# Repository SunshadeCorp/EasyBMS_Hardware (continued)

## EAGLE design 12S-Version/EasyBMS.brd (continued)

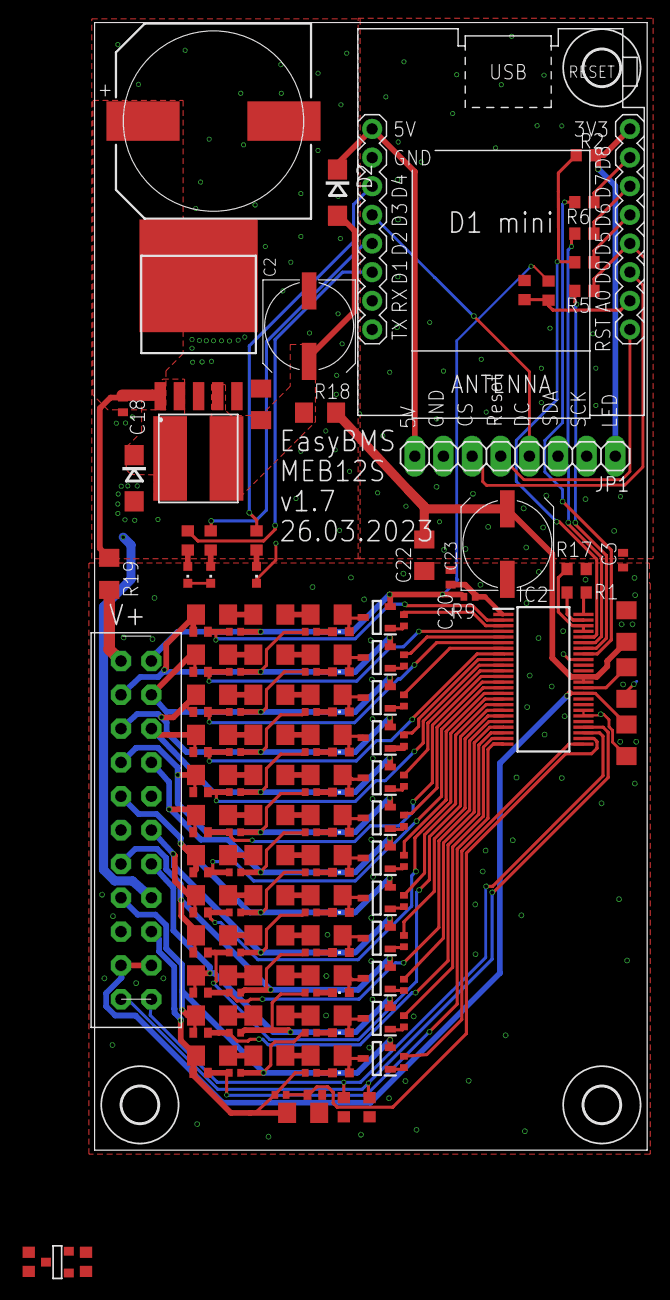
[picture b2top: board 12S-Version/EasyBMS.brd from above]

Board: 2 copper layers, 49.0 x 100.0 mm, 156 parts (0 on the bottom side), 136 nets.

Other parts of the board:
R55, R59: 10k; R0603
T1: C8545; SOT-23

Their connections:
5VINESP: R59.2; also elsewhere on the board
+3V3: R55.2, T1.3; also elsewhere on the board
unnamed: R55.1, T1.2
unnamed: R59.1, T1.1

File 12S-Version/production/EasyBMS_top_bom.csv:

Comment,Designator,Footprint,LCSC Part #
1k,R5 R6 R61 R62,R0603,
1uF,C1 C4 C19 C21 C22,C1206,
3.3k,R10 R22 R28 R34 R40 R46 R52 R68 R74 R80 R87 R93,R0402,
5K1,R2,R0603,
10R0,R4 R7 R8 R14 R20 R21 R25 R26 R27 R31 R32 R33 R37 R38 R39 R43 R44 R45 R49 R50 R51 R65 R66 R67 R71 R72 R73 R77 R78 R79 R84 R85 R86 R90 R91 R92,R1206,
10nF,C5 C6 C7 C8 C9 C10 C11 C12 C13 C14 C15 C16 C17,C0402,
12k,R57 R58,R0603,
20k,R17,R0603,
27K,R16,R0603,
100R,R1,R0603,
100R,R3 R9 R12,R0402,
100R,R19,R1206,
100R,R24 R30 R36 R42 R48 R64 R70 R76 R83 R89 R95,R0402,
100n,C3 C18 C20,C0402,
200R0,R53 R54 R56,R0603,
470R,R11 R23 R29 R35 R41 R47 R63 R69 R75 R81 R88 R94,R0402,
470k,R15,R0603,
BSS84LT1G,Q2 Q3 Q4 Q5 Q6 Q7 Q8 Q9 Q10 Q11 Q12 Q13,SOT96P237X111-3N,
C16015,D1 D2,DO214AC,
C249880,C2 C23,UD-8X10_NICHICON,
C249935,C24,WCAP-ASLI_16X17(DXL),
C370100,R13 R18,R1206,
C2929443,L1,CY75-100UH,
KT-0603R,LED1 LED2 LED4 LED5 LED6 LED7 LED8 LED9 LED11 LED12 LED13 LED14 LED15 LED16 LED17,CHIPLED_0603,
LM2596S-5.0_NOPB,IC1,KTT0005B,
LTC6811IG-1#PBF,IC2,SOP50P780X200-48N,

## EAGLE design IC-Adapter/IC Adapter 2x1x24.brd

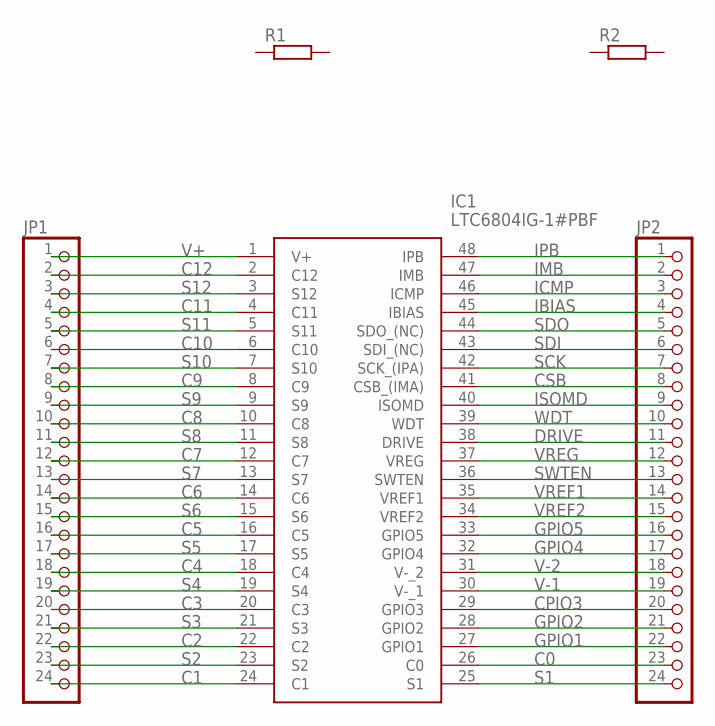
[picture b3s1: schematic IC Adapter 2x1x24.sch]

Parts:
IC1: LTC6804IG-1#PBF; SOP50P780X200-48N
JP1, JP2: PINHD-1X24; 1X24
R1, R2: R-EU_R1210; R1210

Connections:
C0: IC1.26 (C0), JP2.23
C1: IC1.24 (C1), JP1.24
C2: IC1.22 (C2), JP1.22
C3: IC1.20 (C3), JP1.20
C4: IC1.18 (C4), JP1.18
C5: IC1.16 (C5), JP1.16
C6: IC1.14 (C6), JP1.14
C7: IC1.12 (C7), JP1.12
C8: IC1.10 (C8), JP1.10
C9: IC1.8 (C9), JP1.8
C10: IC1.6 (C10), JP1.6
C11: IC1.4 (C11), JP1.4
C12: IC1.2 (C12), JP1.2
CPIO3: IC1.29 (GPIO3), JP2.20
CSB: IC1.41 (CSB_(IMA)), JP2.8
DRIVE: IC1.38 (DRIVE), JP2.11
GPIO1: IC1.27 (GPIO1), JP2.22
GPIO2: IC1.28 (GPIO2), JP2.21
GPIO4: IC1.32 (GPIO4), JP2.17
GPIO5: IC1.33 (GPIO5), JP2.16
IBIAS: IC1.45 (IBIAS), JP2.4
ICMP: IC1.46 (ICMP), JP2.3
IMB: IC1.47 (IMB), JP2.2
IPB: IC1.48 (IPB), JP2.1
ISOMD: IC1.40 (ISOMD), JP2.9
S1: IC1.25 (S1), JP2.24
S2: IC1.23 (S2), JP1.23
S3: IC1.21 (S3), JP1.21
S4: IC1.19 (S4), JP1.19
S5: IC1.17 (S5), JP1.17
S6: IC1.15 (S6), JP1.15
S7: IC1.13 (S7), JP1.13
S8: IC1.11 (S8), JP1.11
S9: IC1.9 (S9), JP1.9
S10: IC1.7 (S10), JP1.7
S11: IC1.5 (S11), JP1.5
S12: IC1.3 (S12), JP1.3
SCK: IC1.42 (SCK_(IPA)), JP2.7
SDI: IC1.43 (SDI_(NC)), JP2.6
SDO: IC1.44 (SDO_(NC)), JP2.5
SWTEN: IC1.36 (SWTEN), JP2.13
V+: IC1.1 (V+), JP1.1
V-1: IC1.30 (V-_1), JP2.19
V-2: IC1.31 (V-_2), JP2.18
VREF1: IC1.35 (VREF1), JP2.14
VREF2: IC1.34 (VREF2), JP2.15
VREG: IC1.37 (VREG), JP2.12
WDT: IC1.39 (WDT), JP2.10

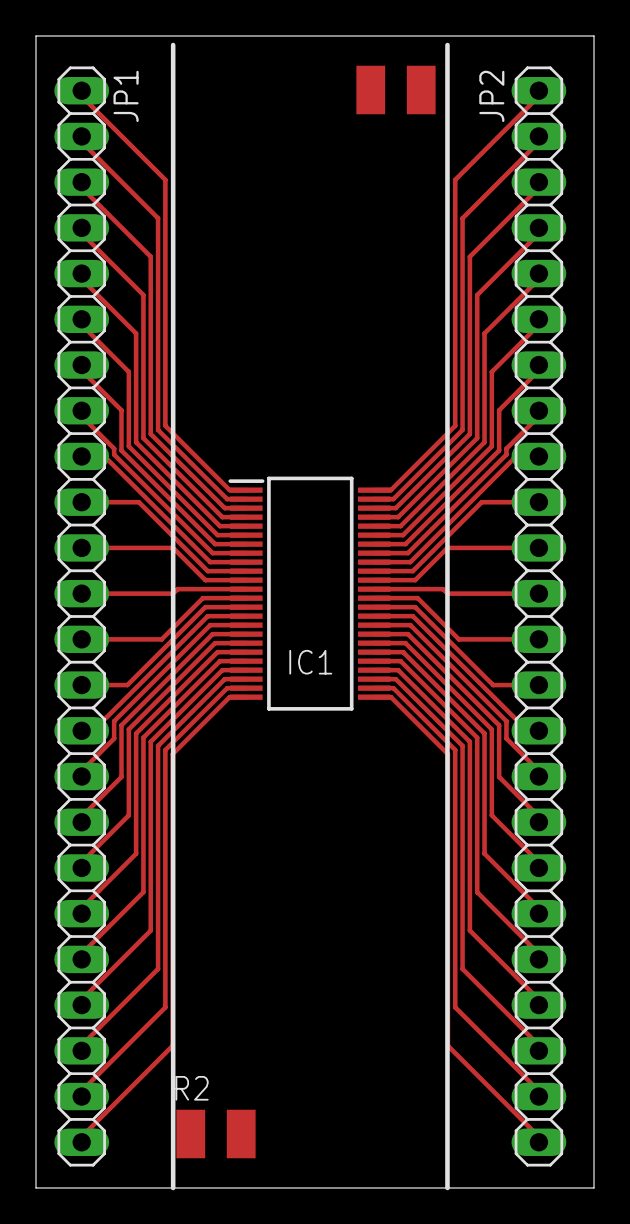
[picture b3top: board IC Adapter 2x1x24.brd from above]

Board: 2 copper layers, 31.0 x 64.0 mm, 5 parts (0 on the bottom side), 48 nets.

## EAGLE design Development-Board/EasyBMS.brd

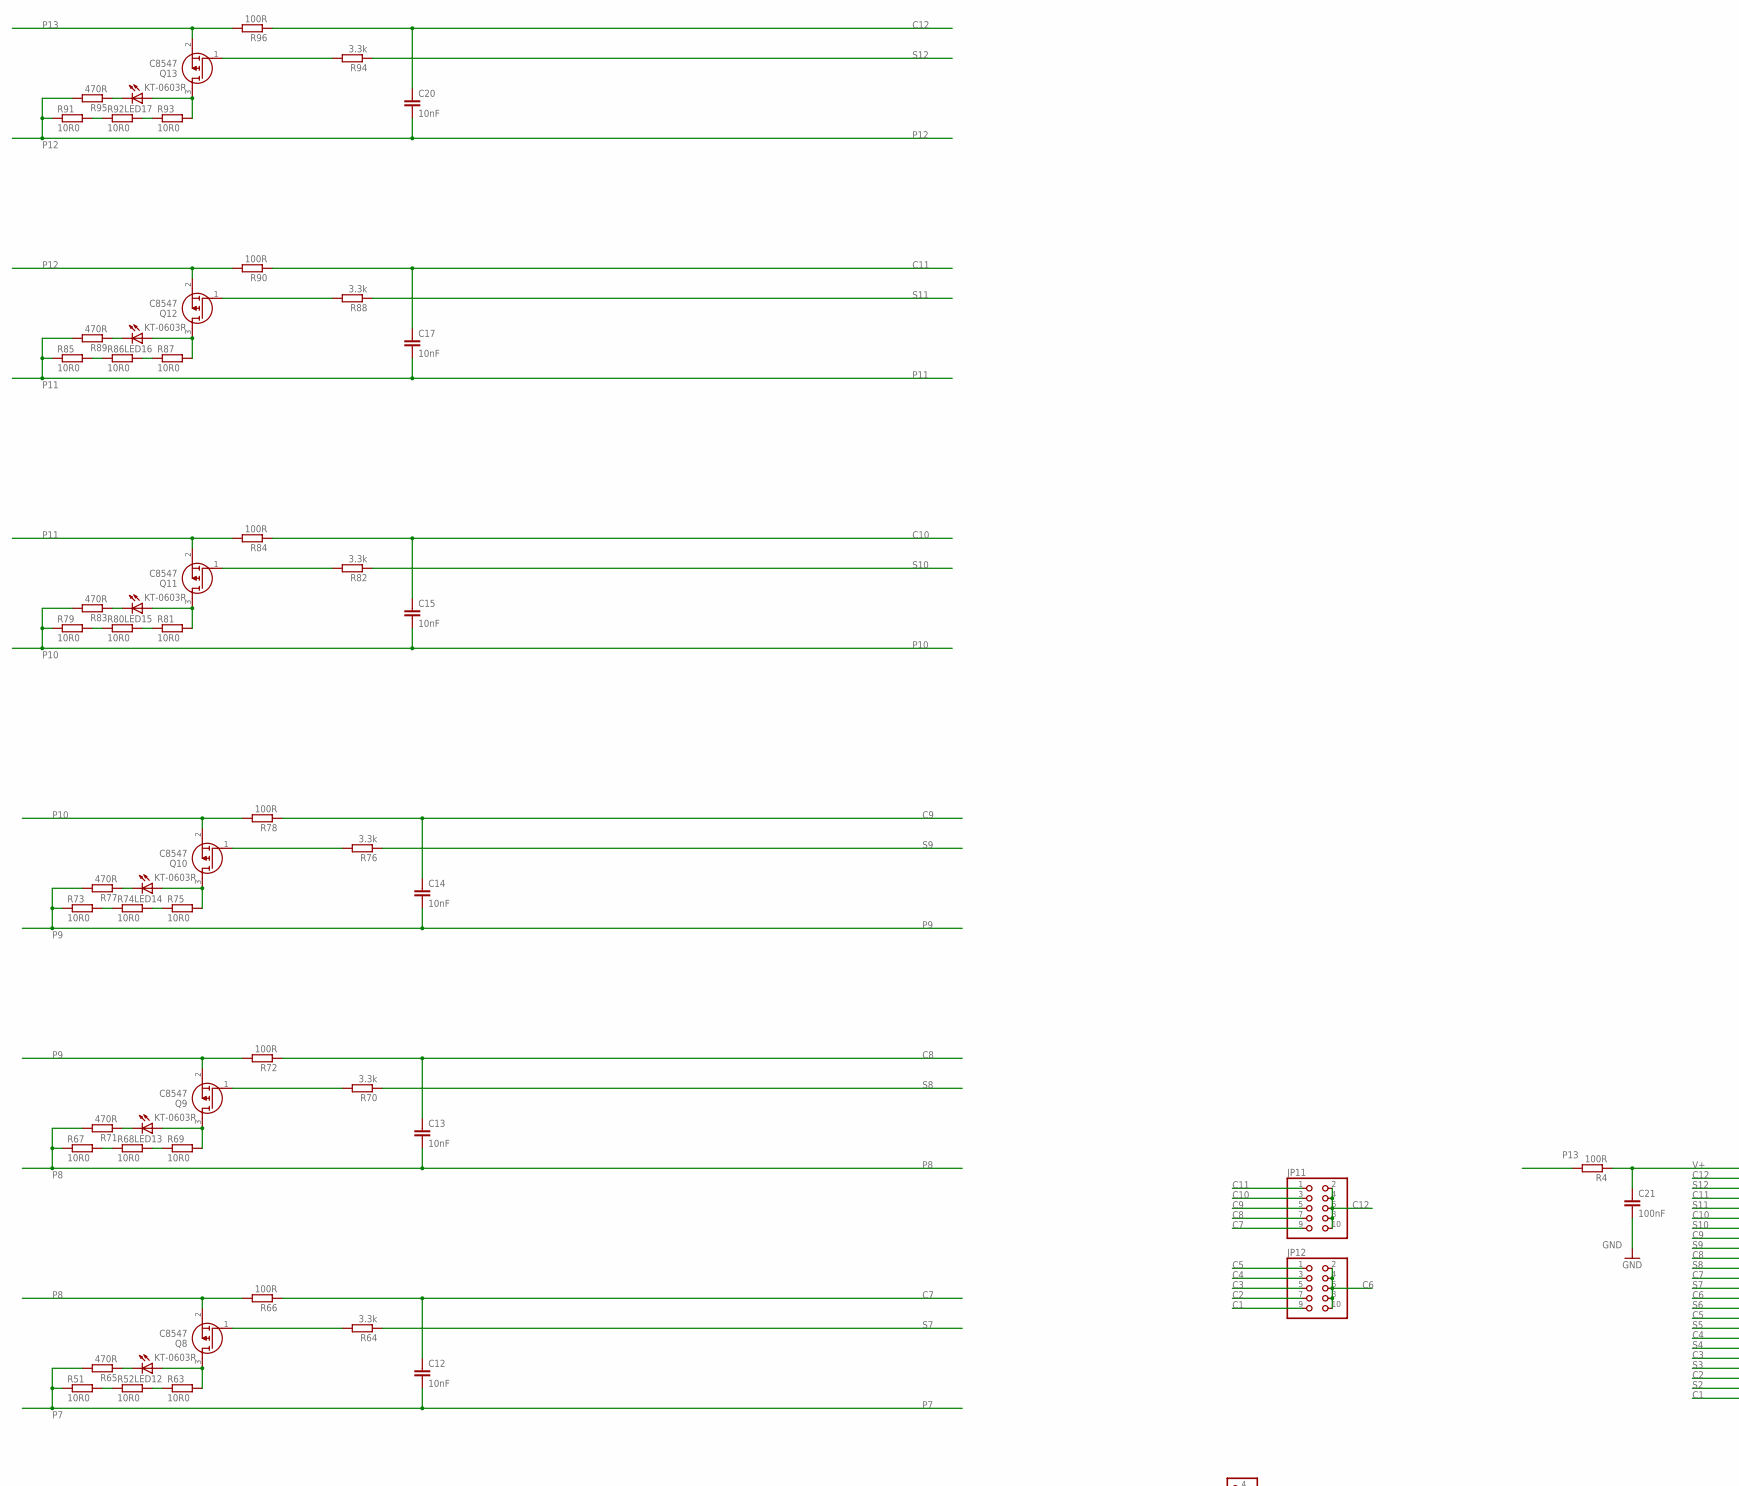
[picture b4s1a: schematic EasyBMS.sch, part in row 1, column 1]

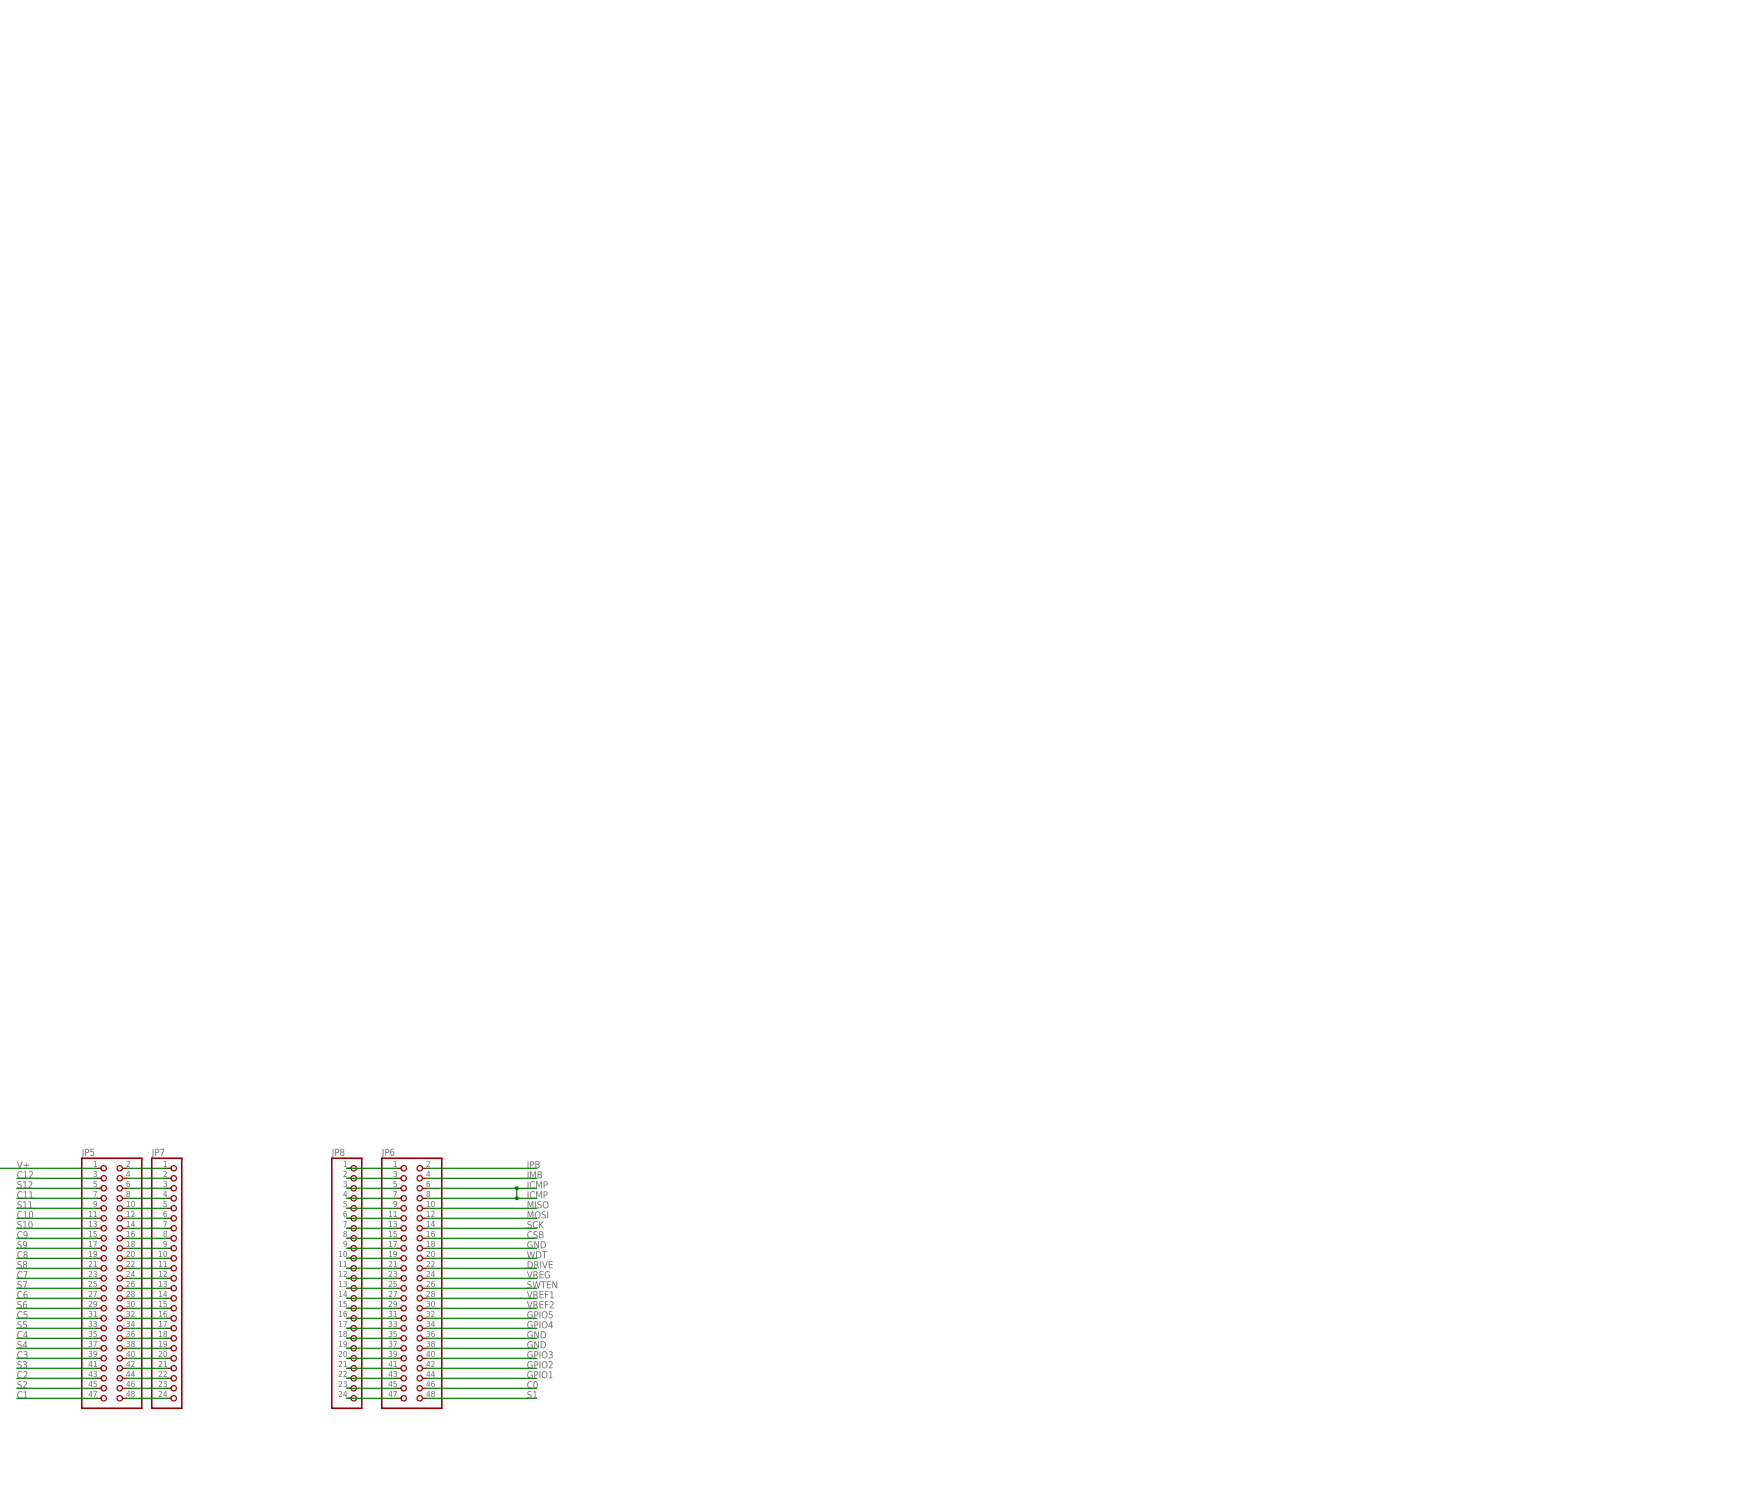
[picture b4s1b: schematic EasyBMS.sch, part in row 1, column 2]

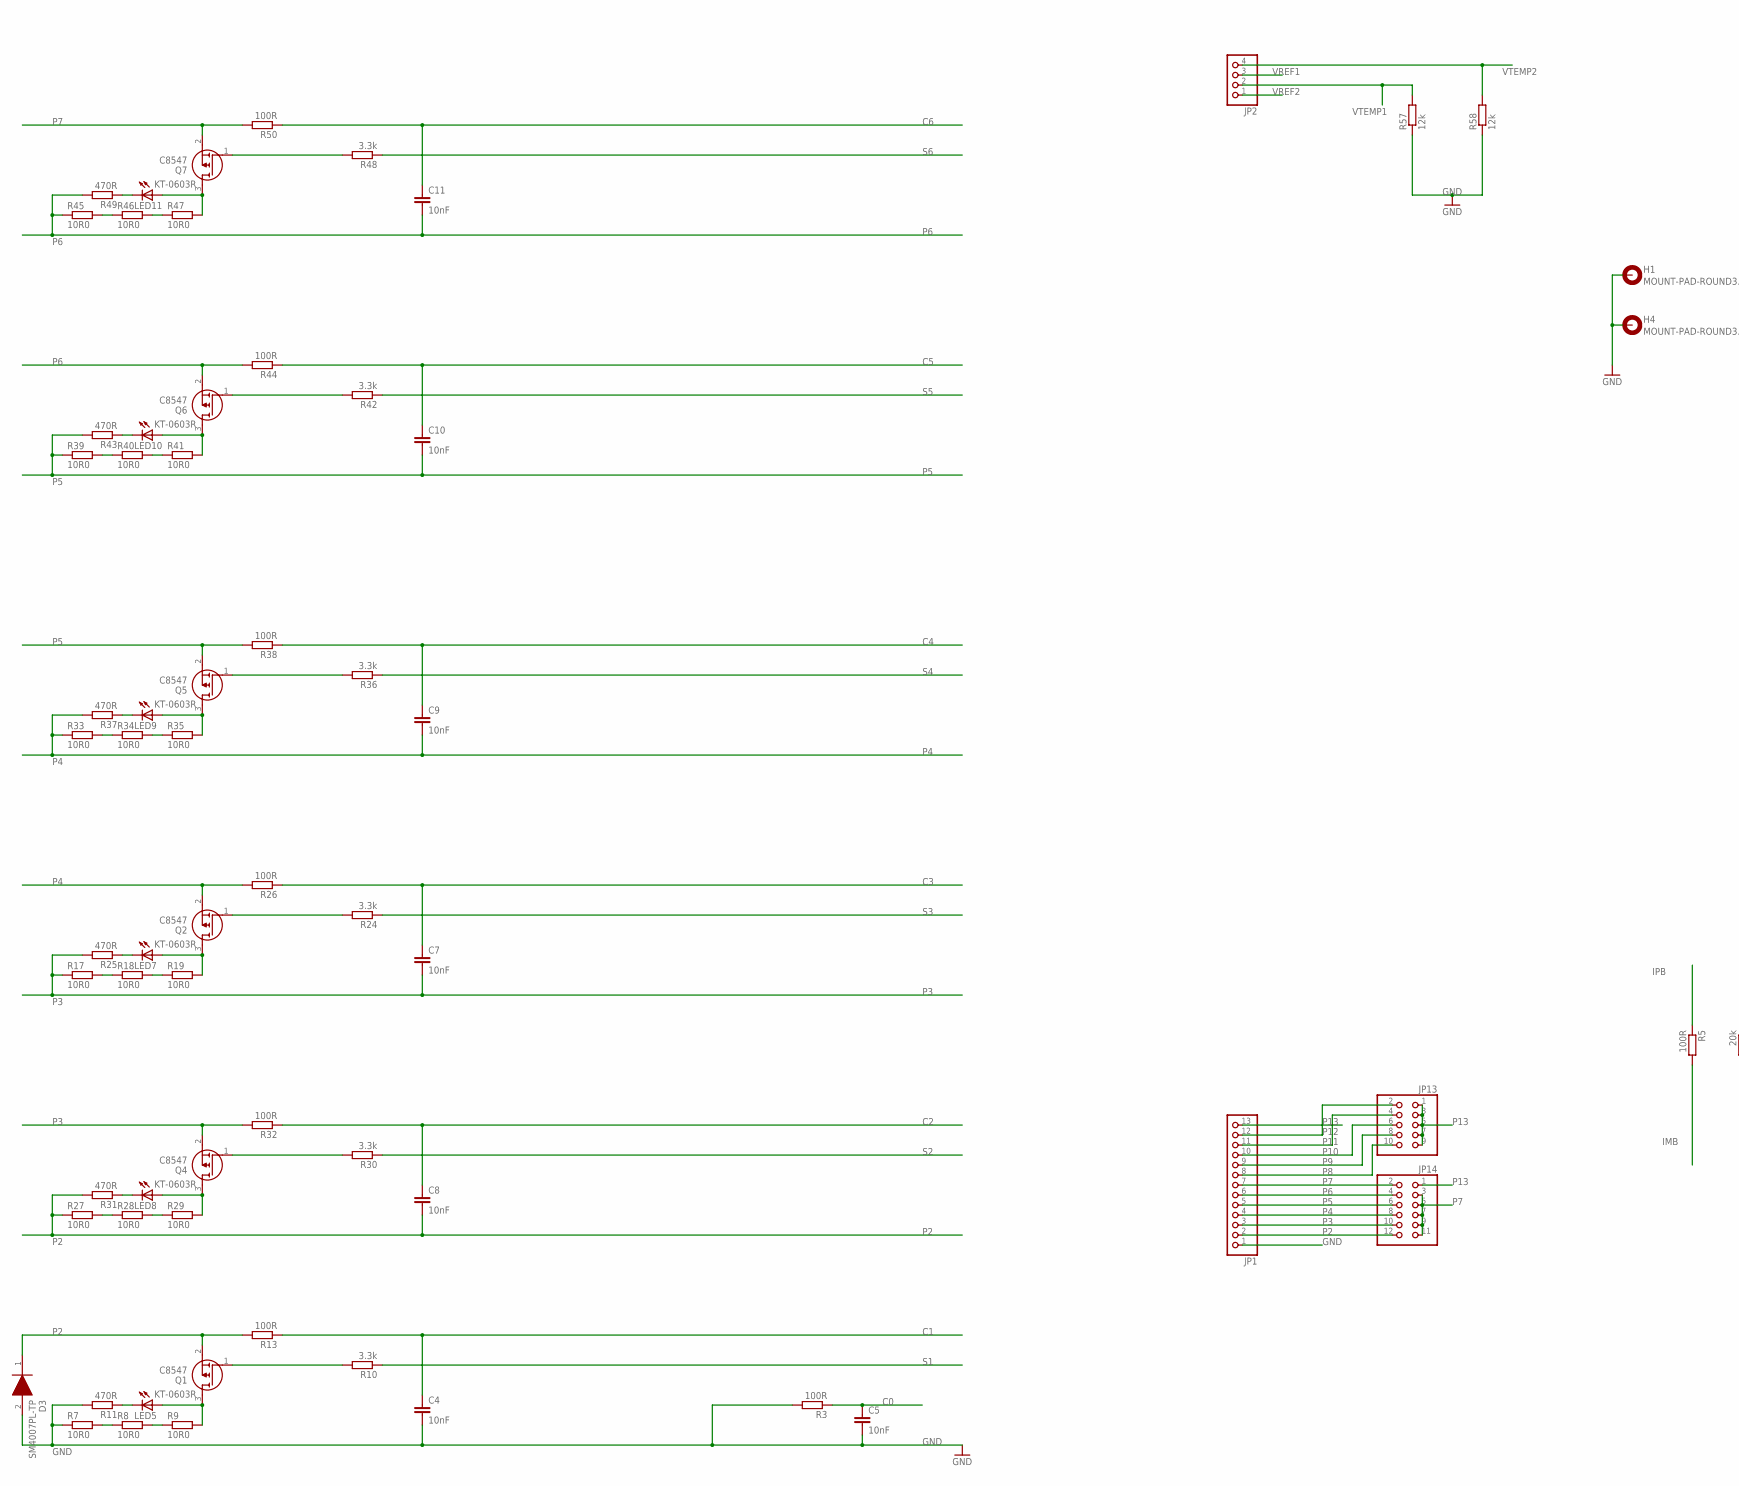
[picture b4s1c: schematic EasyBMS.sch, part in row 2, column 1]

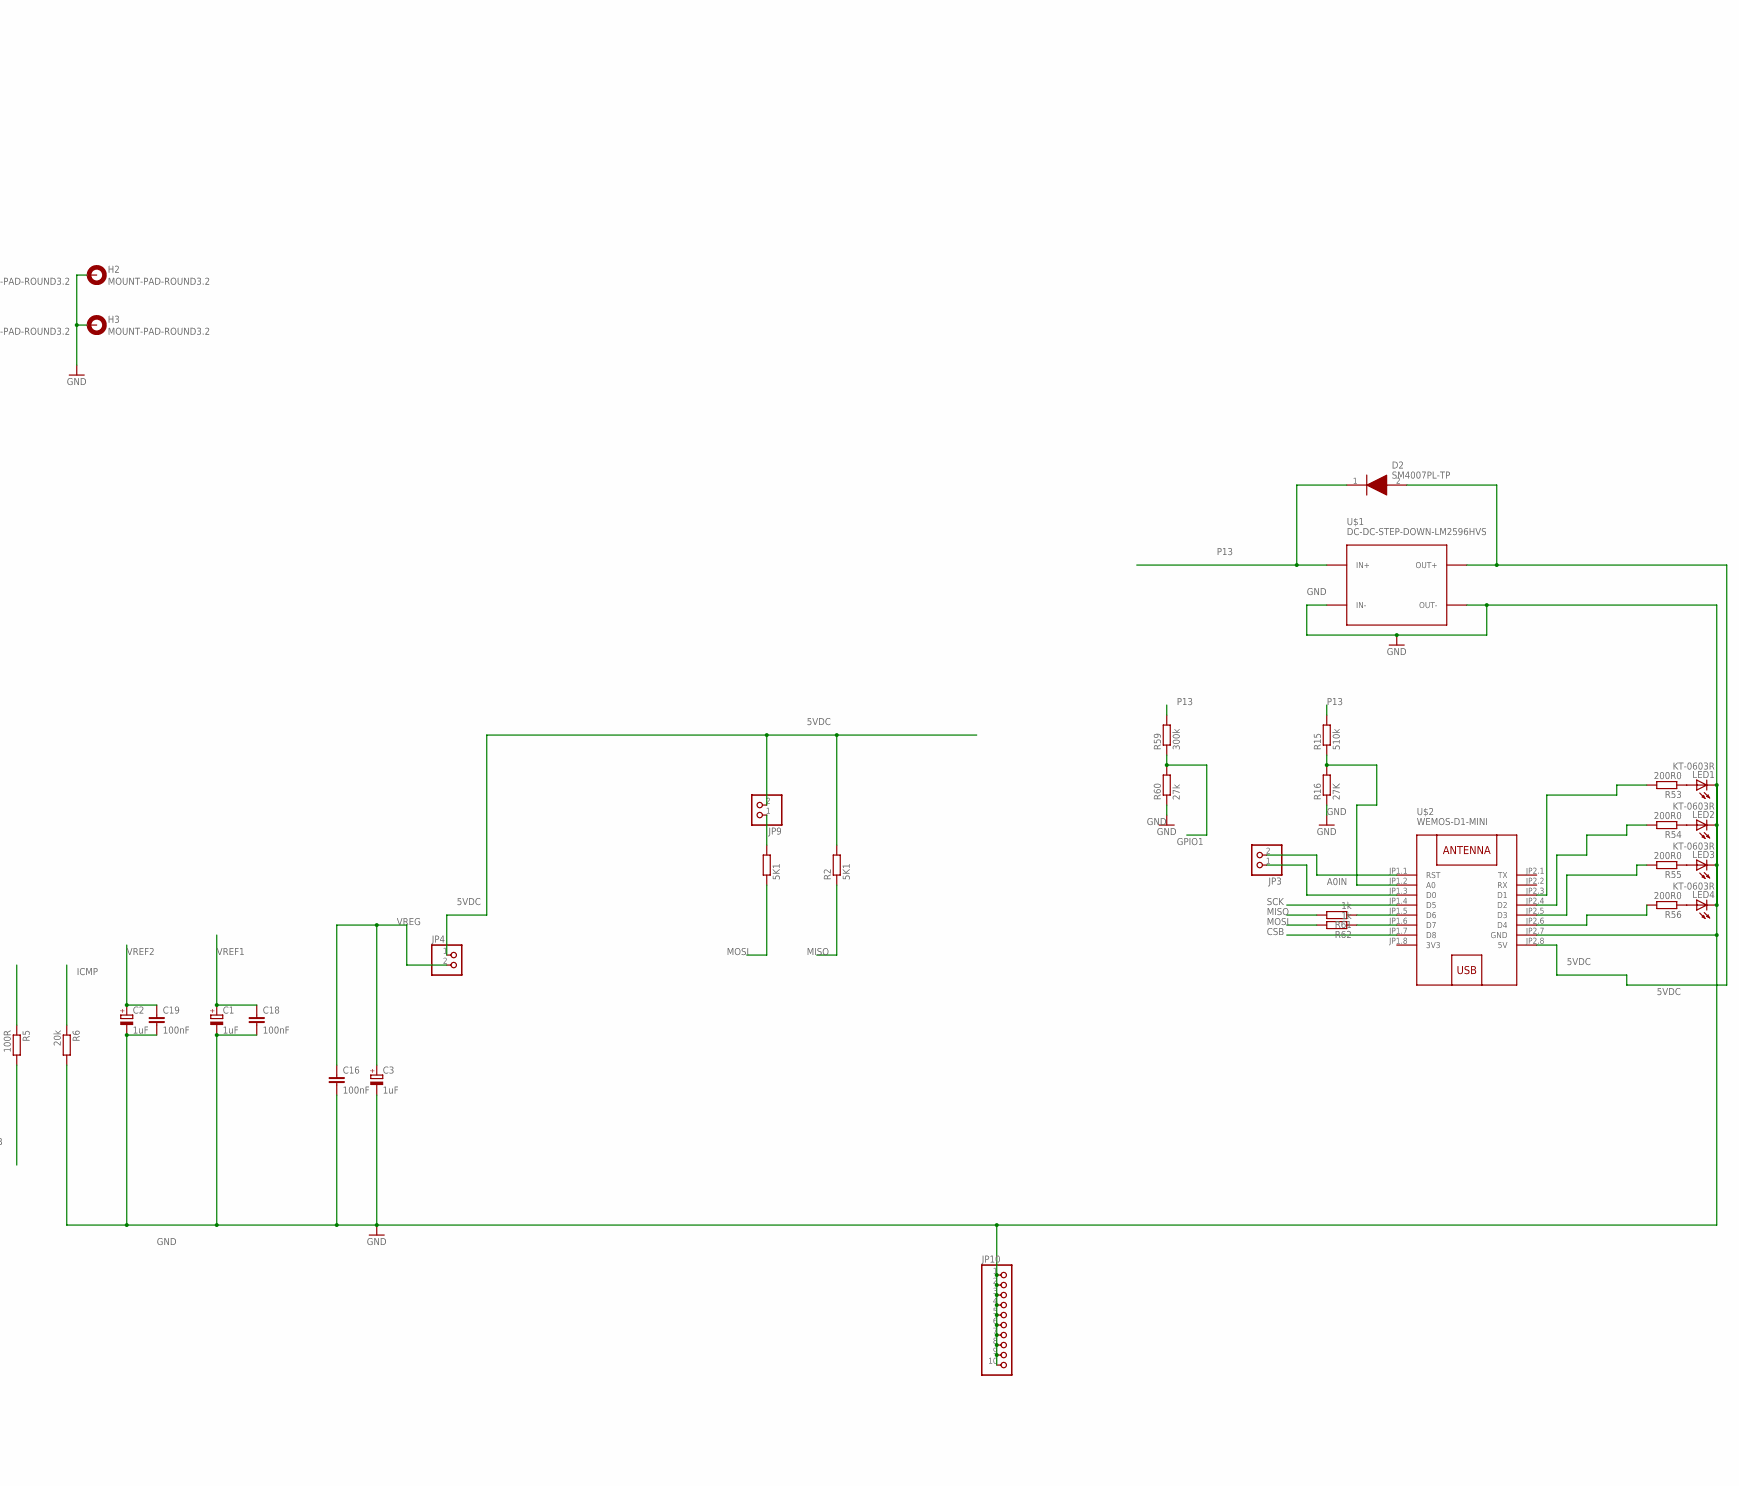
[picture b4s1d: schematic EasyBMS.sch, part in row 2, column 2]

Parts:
C1, C2, C3: 1uF; E2,5-6
C4, C5, C7, C8, C9, C10, C11, C12, C13, C14, C15, C17, C20: 10nF; C0402
C16, C18, C19, C21: 100nF; C1206
D2, D3: SM4007PL-TP; SODFL3616X135N
H1, H2, H3, H4: MOUNT-PAD-ROUND3.2; 3,2-PAD
JP1: PINHD-1X13/90; 1X13/90
JP2: PINHD-1X4/90; 1X04/90
JP3, JP4, JP9: PINHD-1X2; 1X02
JP5, JP6: PINHD-2X24; 2X24
JP7, JP8: PINHD-1X24; 1X24
JP10: PINHD-1X10; 1X10
JP11, JP12, JP13: PINHD-2X5; 2X05
JP14: PINHD-2X6; 2X06
LED1, LED2, LED3, LED4, LED5, LED7, LED8, LED9, LED10, LED11, LED12, LED13, LED14, LED15, LED16, LED17: KT-0603R; CHIPLED_0603
Q1, Q2, Q4, Q5, Q6, Q7, Q8, Q9, Q10, Q11, Q12, Q13: C8547; PG-SOT-23
R1, R2: 5K1; R0603
R3, R4, R5, R13, R26, R32, R38, R44, R50, R66, R72, R78, R84, R90, R96: 100R; R0402
R6: 20k; R0603
R7, R8, R9, R17, R18, R19, R27, R28, R29, R33, R34, R35, R39, R40, R41, R45, R46, R47, R51, R52, R63, R67, R68, R69, R73, R74, R75, R79, R80, R81, R85, R86, R87, R91, R92, R93: 10R0; R1206
R10, R24, R30, R36, R42, R48, R64, R70, R76, R82, R88, R94: 3.3k; R0402
R11, R25, R31, R37, R43, R49, R65, R71, R77, R83, R89, R95: 470R; R0402
R15: 510k; R0603
R16: 27K; R0603
R53, R54, R55, R56: 200R0; R0603
R57, R58: 12k; R0603
R59: 300k; R0603
R60: 27k; R0603
R61, R62: 1k; R0603
U$1: DC-DC-STEP-DOWN-LM2596HVS
U$2: WEMOS-D1-MINI

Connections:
3V3: U$2.JP1.8 (3V3)
5VDC: D2.2 (A), JP4.1, JP9.2, R2.2, U$1.OUT+, U$2.JP2.8 (5V)
A0IN: R15.1, R16.2, U$2.JP1.2 (A0)
C0: C5.1, JP6.46, R3.1
C1: C4.1, JP5.47, JP12.9, R13.1
C2: C8.1, JP5.43, JP12.7, R32.1
C3: C7.1, JP5.39, JP12.5, R26.1
C4: C9.1, JP5.35, JP12.3, R38.1
C5: C10.1, JP5.31, JP12.1, R44.1
C6: C11.1, JP5.27, JP12.2, JP12.4, JP12.6, JP12.8, JP12.10, R50.1
C7: C12.1, JP5.23, JP11.9, R66.1
C8: C13.1, JP5.19, JP11.7, R72.1
C9: C14.1, JP5.15, JP11.5, R78.1
C10: C15.1, JP5.11, JP11.3, R84.1
C11: C17.1, JP5.7, JP11.1, R90.1
C12: C20.1, JP5.3, JP11.2, JP11.4, JP11.6, JP11.8, JP11.10, R96.1
CSB: JP6.16, U$2.JP1.7 (D8)
DRIVE: JP6.22
GND: C1.-, C2.-, C3.-, C4.2, C5.2, C16.2, C18.2, C19.2, C21.2, D3.2 (A), H1.B3,2, H2.B3,2, H3.B3,2, H4.B3,2, JP1.1, JP6.18, JP6.36, JP6.38, JP10.1, JP10.2, JP10.3, JP10.4, JP10.5, JP10.6, JP10.7, JP10.8, JP10.9, JP10.10, LED1.C, LED2.C, LED3.C, LED4.C, R3.2, R6.2, R7.1, R11.2, R16.1, R57.1, R58.1, R60.1, U$1.IN-, U$1.OUT-, U$2.JP2.7 (GND)
GPIO1: JP6.44, R59.1, R60.2
GPIO2: JP6.42
GPIO3: JP6.40
GPIO4: JP6.34
GPIO5: JP6.32
ICMP: JP6.6, JP6.8, R6.1
IMB: JP6.4, R5.2
IPB: JP6.2, R5.1
MISO: JP6.10, R2.1, R61.2
MOSI: JP6.12, R1.1, R62.2
unnamed: LED1.A, R53.1
unnamed: LED2.A, R54.1
unnamed: LED3.A, R55.1
unnamed: LED4.A, R56.1
unnamed: JP3.2, U$2.JP1.1 (RST)
unnamed: JP3.1, U$2.JP1.3 (D0)
unnamed: JP5.48, JP7.24
unnamed: JP5.46, JP7.23
unnamed: JP5.44, JP7.22
unnamed: JP5.42, JP7.21
unnamed: JP5.40, JP7.20
unnamed: JP5.38, JP7.19
unnamed: JP5.36, JP7.18
unnamed: R7.2, R8.1
unnamed: R8.2, R9.1
unnamed: JP5.34, JP7.17
unnamed: LED5.A, Q1.3 (D), R9.2
unnamed: JP5.32, JP7.16
unnamed: Q1.1 (G), R10.2
unnamed: LED5.C, R11.1
unnamed: R17.2, R18.1
unnamed: R18.2, R19.1
unnamed: LED7.A, Q2.3 (D), R19.2
unnamed: R56.2, U$2.JP2.6 (D4)
unnamed: Q2.1 (G), R24.2
unnamed: LED7.C, R25.1
unnamed: R27.2, R28.1
unnamed: R28.2, R29.1
unnamed: LED8.A, Q4.3 (D), R29.2
unnamed: Q4.1 (G), R30.2
unnamed: LED8.C, R31.1
unnamed: R33.2, R34.1
unnamed: R34.2, R35.1
unnamed: LED9.A, Q5.3 (D), R35.2
unnamed: Q5.1 (G), R36.2
unnamed: LED9.C, R37.1
unnamed: R39.2, R40.1
unnamed: R40.2, R41.1
unnamed: LED10.A, Q6.3 (D), R41.2
unnamed: Q6.1 (G), R42.2
unnamed: LED10.C, R43.1
unnamed: R45.2, R46.1
unnamed: R46.2, R47.1
unnamed: LED11.A, Q7.3 (D), R47.2
unnamed: Q7.1 (G), R48.2
unnamed: LED11.C, R49.1
unnamed: R51.2, R52.1
unnamed: R52.2, R63.1
unnamed: LED12.A, Q8.3 (D), R63.2
unnamed: Q8.1 (G), R64.2
unnamed: LED12.C, R65.1
unnamed: R67.2, R68.1
unnamed: R68.2, R69.1
unnamed: LED13.A, Q9.3 (D), R69.2
unnamed: JP5.30, JP7.15
unnamed: Q9.1 (G), R70.2
unnamed: LED13.C, R71.1
unnamed: R73.2, R74.1
unnamed: R74.2, R75.1
unnamed: LED14.A, Q10.3 (D), R75.2
unnamed: Q10.1 (G), R76.2
unnamed: LED14.C, R77.1
unnamed: R79.2, R80.1
unnamed: R53.2, U$2.JP2.3 (D1)
unnamed: R80.2, R81.1
unnamed: LED15.A, Q11.3 (D), R81.2
unnamed: R61.1, U$2.JP1.5 (D6)
unnamed: JP5.28, JP7.14
unnamed: JP5.26, JP7.13
unnamed: JP5.24, JP7.12
unnamed: JP5.22, JP7.11
unnamed: JP5.20, JP7.10
unnamed: Q11.1 (G), R82.2
unnamed: LED15.C, R83.1
unnamed: R85.2, R86.1
unnamed: R86.2, R87.1
unnamed: LED16.A, Q12.3 (D), R87.2
unnamed: JP5.18, JP7.9
unnamed: JP5.16, JP7.8
unnamed: JP5.14, JP7.7
unnamed: JP5.12, JP7.6
unnamed: JP5.10, JP7.5
unnamed: JP5.8, JP7.4
unnamed: JP5.6, JP7.3
unnamed: JP5.4, JP7.2
unnamed: JP6.47, JP8.24
unnamed: JP6.45, JP8.23
unnamed: JP6.43, JP8.22
unnamed: JP6.41, JP8.21
unnamed: JP6.39, JP8.20
unnamed: JP6.37, JP8.19
unnamed: JP6.35, JP8.18
unnamed: JP6.33, JP8.17
unnamed: JP6.31, JP8.16
unnamed: JP6.29, JP8.15
unnamed: JP6.27, JP8.14
unnamed: JP6.25, JP8.13
unnamed: JP6.23, JP8.12
unnamed: JP6.21, JP8.11
unnamed: JP6.19, JP8.10
unnamed: JP6.17, JP8.9
unnamed: JP6.15, JP8.8
unnamed: JP6.13, JP8.7
unnamed: JP6.11, JP8.6
unnamed: JP6.9, JP8.5
unnamed: JP6.7, JP8.4
unnamed: JP6.5, JP8.3
unnamed: JP6.3, JP8.2
unnamed: JP6.1, JP8.1
unnamed: JP9.1, R1.2
unnamed: JP5.2, JP7.1
unnamed: R62.1, U$2.JP1.6 (D7)
unnamed: R55.2, U$2.JP2.5 (D3)
unnamed: Q12.1 (G), R88.2
unnamed: LED16.C, R89.1
unnamed: R54.2, U$2.JP2.4 (D2)
unnamed: R91.2, R92.1
unnamed: R92.2, R93.1
unnamed: LED17.A, Q13.3 (D), R93.2
unnamed: Q13.1 (G), R94.2
unnamed: LED17.C, R95.1
P2: C8.2, D3.1 (K), JP1.2, JP14.12, Q1.2 (S), R13.2, R27.1, R31.2
P3: C7.2, JP1.3, JP14.10, Q4.2 (S), R17.1, R25.2, R32.2
P4: C9.2, JP1.4, JP14.8, Q2.2 (S), R26.2, R33.1, R37.2
P5: C10.2, JP1.5, JP14.6, Q5.2 (S), R38.2, R39.1, R43.2
P6: C11.2, JP1.6, JP14.4, Q6.2 (S), R44.2, R45.1, R49.2
P7: C12.2, JP1.7, JP14.2, JP14.3, JP14.5, JP14.7, JP14.9, JP14.11, Q7.2 (S), R50.2, R51.1, R65.2
P8: C13.2, JP1.8, JP13.10, Q8.2 (S), R66.2, R67.1, R71.2
P9: C14.2, JP1.9, JP13.8, Q9.2 (S), R72.2, R73.1, R77.2
P10: C15.2, JP1.10, JP13.6, Q10.2 (S), R78.2, R79.1, R83.2
P11: C17.2, JP1.11, JP13.4, Q11.2 (S), R84.2, R85.1, R89.2
P12: C20.2, JP1.12, JP13.2, Q12.2 (S), R90.2, R91.1, R95.2
P13: D2.1 (K), JP1.13, JP13.1, JP13.3, JP13.5, JP13.7, JP13.9, JP14.1, Q13.2 (S), R4.2, R15.2, R59.2, R96.2, U$1.IN+
S1: JP6.48, R10.1
S2: JP5.45, R30.1
S3: JP5.41, R24.1
S4: JP5.37, R36.1
S5: JP5.33, R42.1
S6: JP5.29, R48.1
S7: JP5.25, R64.1
S8: JP5.21, R70.1
S9: JP5.17, R76.1
S10: JP5.13, R82.1
S11: JP5.9, R88.1
S12: JP5.5, R94.1
SCK: JP6.14, U$2.JP1.4 (D5)
SWTEN: JP6.26
V+: C21.1, JP5.1, R4.1
VREF1: C1.+, C18.1, JP2.3, JP6.28
VREF2: C2.+, C19.1, JP2.1, JP6.30
VREG: C3.+, C16.1, JP4.2, JP6.24
VTEMP1: JP2.2, R57.2
VTEMP2: JP2.4, R58.2
WDT: JP6.20

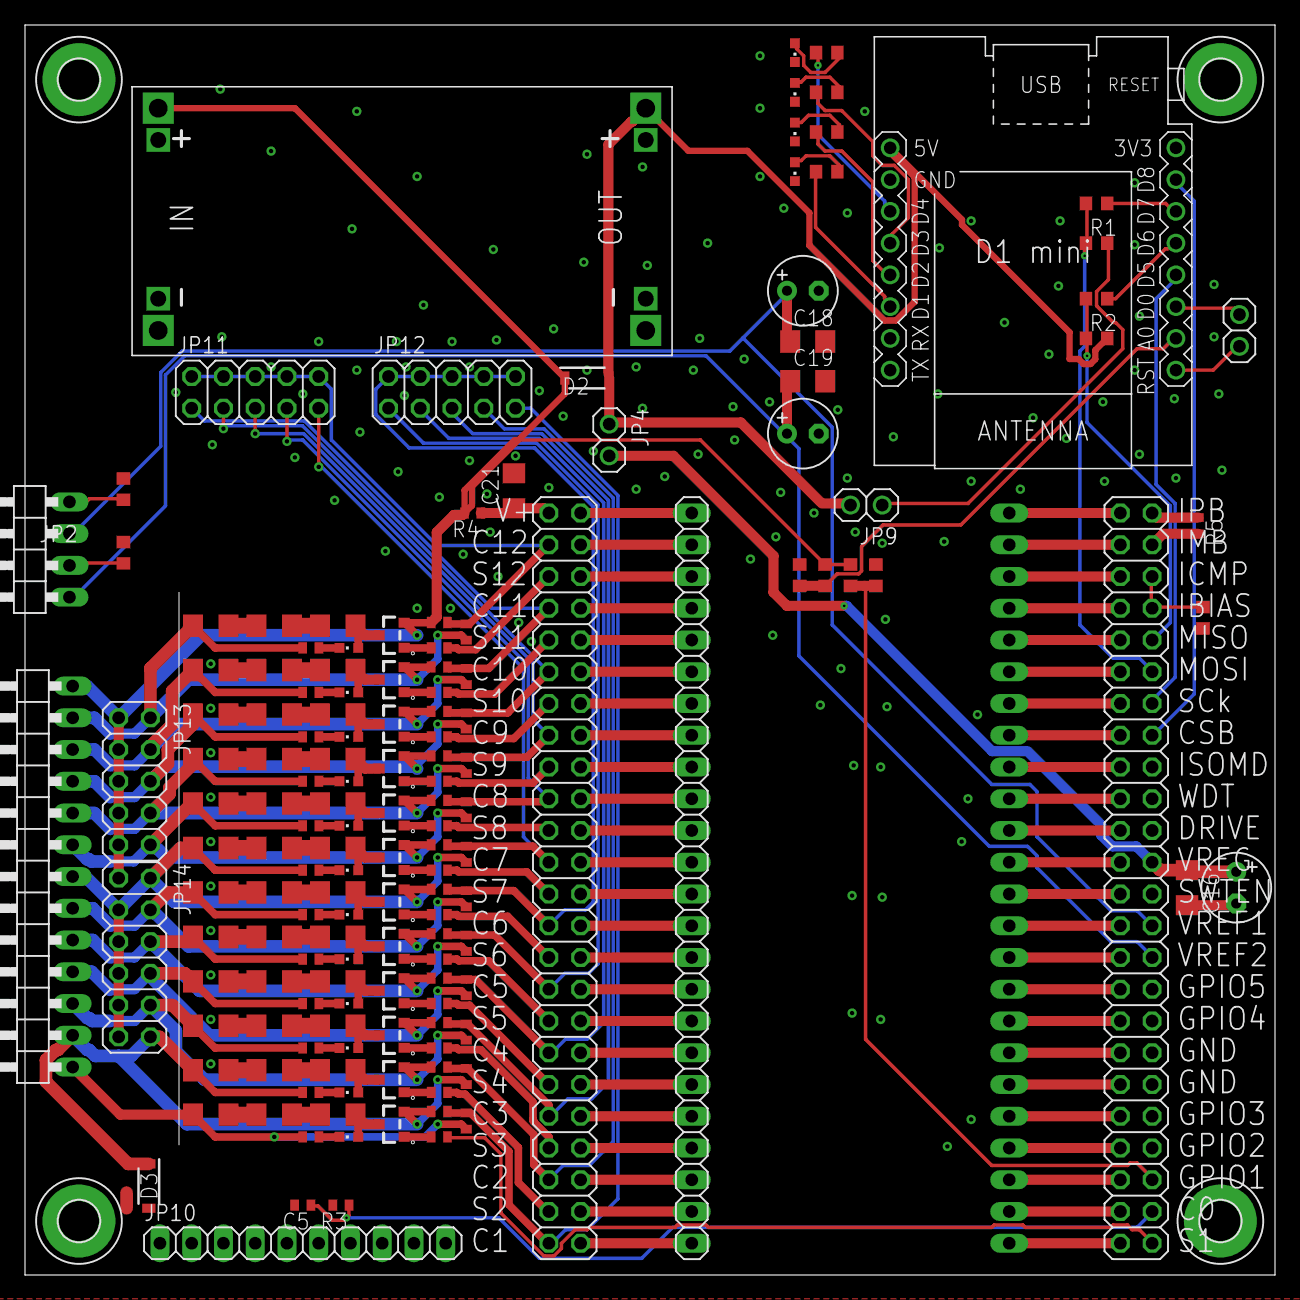
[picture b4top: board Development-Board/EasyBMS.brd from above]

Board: 2 copper layers, 100.0 x 100.0 mm, 160 parts (1 on the bottom side), 175 nets.

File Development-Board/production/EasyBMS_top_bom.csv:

Comment,Designator,Footprint,LCSC Part #
1k,R61 R62,R0603,
3.3k,R10 R24 R30 R36 R42 R48 R64 R70 R76 R82 R88 R94,R0402,
5K1,R1 R2,R0603,
10R0,R7 R8 R9 R17 R18 R19 R27 R28 R29 R33 R34 R35 R39 R40 R41 R45 R46 R47 R51 R52 R63 R67 R68 R69 R73 R74 R75 R79 R80 R81 R85 R86 R87 R91 R92 R93,R1206,
10nF,C4 C5 C7 C8 C9 C10 C11 C12 C13 C14 C15 C17 C20,C0402,
12k,R57 R58,R0603,
20k,R6,R0603,
27K,R16,R0603,
27k,R60,R0603,
100R,R3 R4 R5 R13 R26 R32 R38 R44 R50 R66 R72 R78 R84 R90 R96,R0402,
100nF,C16 C18 C19 C21,C1206,
200R0,R53 R54 R55 R56,R0603,
300k,R59,R0603,
470R,R11 R25 R31 R37 R43 R49 R65 R71 R77 R83 R89 R95,R0402,
510k,R15,R0603,
C8547,Q1 Q2 Q4 Q5 Q6 Q7 Q8 Q9 Q10 Q11 Q12 Q13,PG-SOT-23,
KT-0603R,LED1 LED2 LED3 LED4 LED5 LED7 LED8 LED9 LED10 LED11 LED12 LED13 LED14 LED15 LED16 LED17,CHIPLED_0603,
SM4007PL-TP,D2 D3,SODFL3616X135N,

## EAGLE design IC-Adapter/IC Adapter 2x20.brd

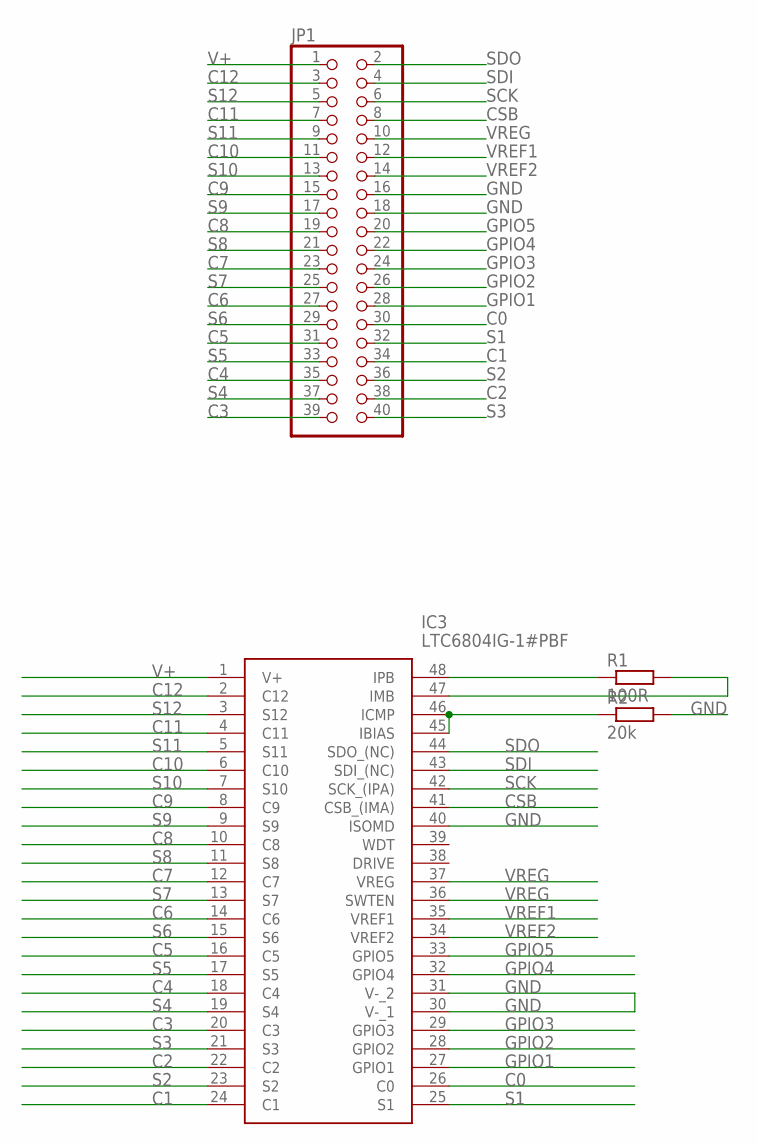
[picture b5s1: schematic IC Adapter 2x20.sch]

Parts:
IC3: LTC6804IG-1#PBF; SOP50P780X200-48N
JP1: PINHD-2X20; 2X20
R1: 100R; R0805
R2: 20k; R0805

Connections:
C0: IC3.26 (C0), JP1.30
C1: IC3.24 (C1), JP1.34
C2: IC3.22 (C2), JP1.38
C3: IC3.20 (C3), JP1.39
C4: IC3.18 (C4), JP1.35
C5: IC3.16 (C5), JP1.31
C6: IC3.14 (C6), JP1.27
C7: IC3.12 (C7), JP1.23
C8: IC3.10 (C8), JP1.19
C9: IC3.8 (C9), JP1.15
C10: IC3.6 (C10), JP1.11
C11: IC3.4 (C11), JP1.7
C12: IC3.2 (C12), JP1.3
CSB: IC3.41 (CSB_(IMA)), JP1.8
GND: IC3.30 (V-_1), IC3.31 (V-_2), IC3.40 (ISOMD), JP1.16, JP1.18, R2.2
GPIO1: IC3.27 (GPIO1), JP1.28
GPIO2: IC3.28 (GPIO2), JP1.26
GPIO3: IC3.29 (GPIO3), JP1.24
GPIO4: IC3.32 (GPIO4), JP1.22
GPIO5: IC3.33 (GPIO5), JP1.20
ICMP: IC3.45 (IBIAS), IC3.46 (ICMP), R2.1
unnamed: IC3.48 (IPB), R1.1
unnamed: IC3.47 (IMB), R1.2
S1: IC3.25 (S1), JP1.32
S2: IC3.23 (S2), JP1.36
S3: IC3.21 (S3), JP1.40
S4: IC3.19 (S4), JP1.37
S5: IC3.17 (S5), JP1.33
S6: IC3.15 (S6), JP1.29
S7: IC3.13 (S7), JP1.25
S8: IC3.11 (S8), JP1.21
S9: IC3.9 (S9), JP1.17
S10: IC3.7 (S10), JP1.13
S11: IC3.5 (S11), JP1.9
S12: IC3.3 (S12), JP1.5
SCK: IC3.42 (SCK_(IPA)), JP1.6
SDI: IC3.43 (SDI_(NC)), JP1.4
SDO: IC3.44 (SDO_(NC)), JP1.2
V+: IC3.1 (V+), JP1.1
VREF1: IC3.35 (VREF1), JP1.12
VREF2: IC3.34 (VREF2), JP1.14
VREG: IC3.36 (SWTEN), IC3.37 (VREG), JP1.10
